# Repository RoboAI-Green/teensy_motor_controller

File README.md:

# teensy_motor_controller
Teensy Motor Controller

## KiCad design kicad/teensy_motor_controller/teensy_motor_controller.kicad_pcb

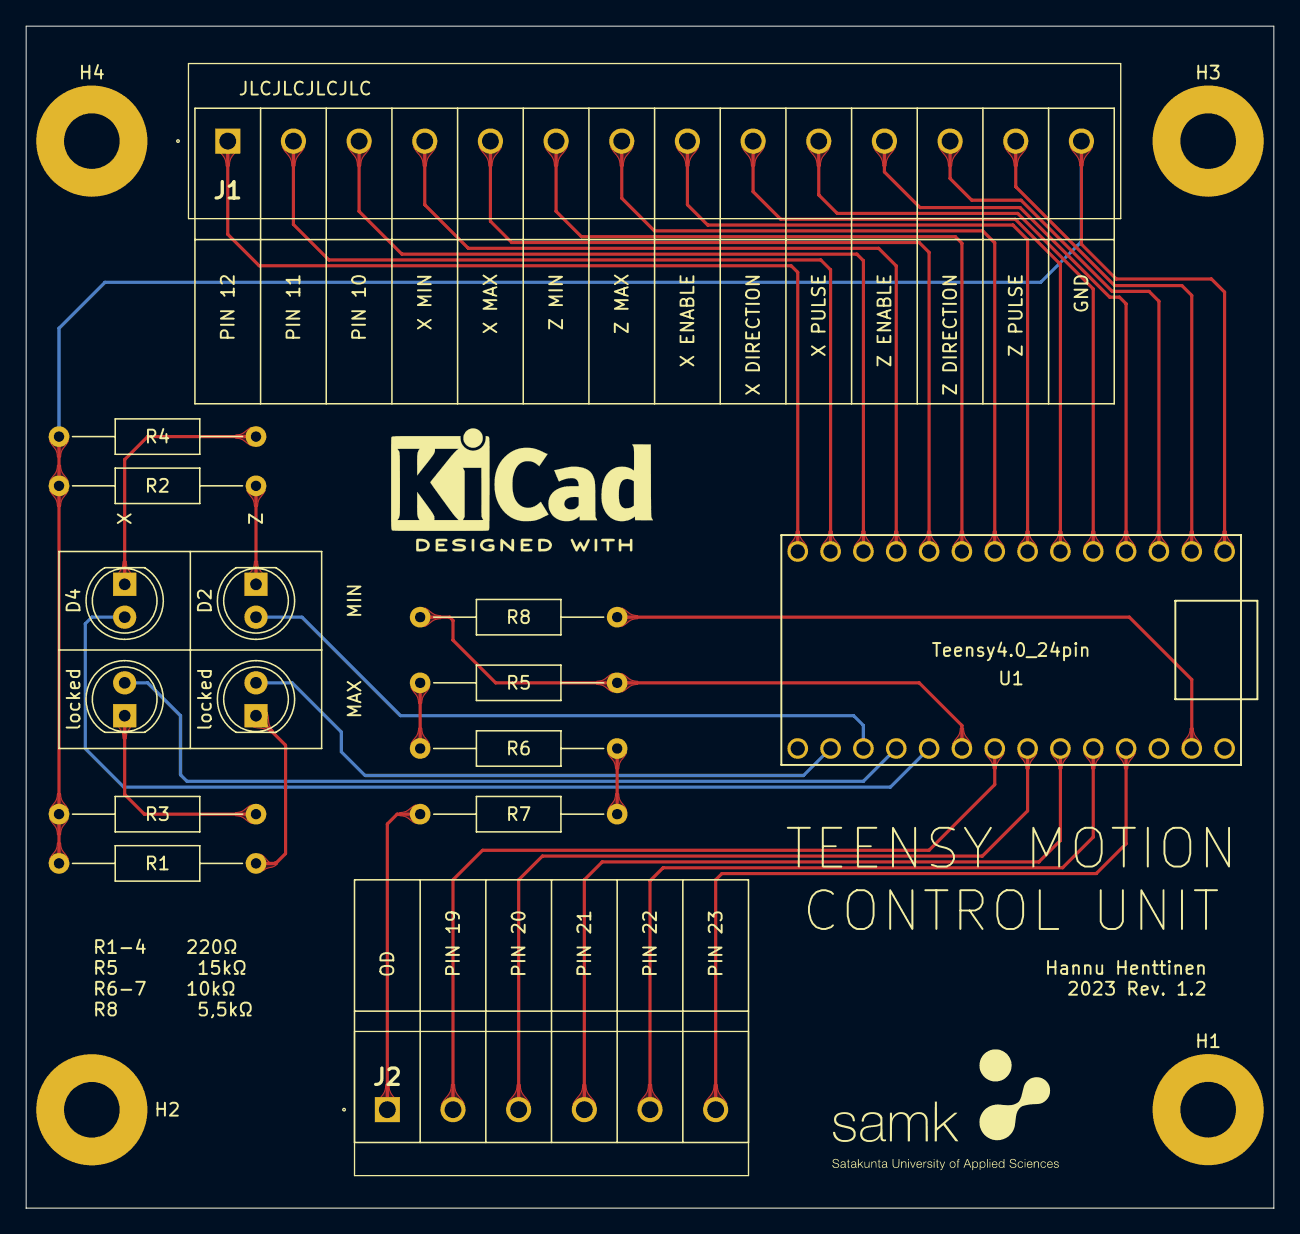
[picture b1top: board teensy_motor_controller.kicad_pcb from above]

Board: 2 copper layers, 96.5 x 91.4 mm, 19 parts (0 on the bottom side), 32 nets.

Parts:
D2, D4: LED; LED_D5.0mm
H1, H2, H3, H4: MountingHole; MountingHole_4.3mm_M4_Pad
J1: 1869334
J2: 1730162
R1, R2, R3, R4: 220; R_Axial_DIN0207_L6.3mm_D2.5mm_P15.24mm_Horizontal
R5: R15k; R_Axial_DIN0207_L6.3mm_D2.5mm_P15.24mm_Horizontal
R6, R7: R10k; R_Axial_DIN0207_L6.3mm_D2.5mm_P15.24mm_Horizontal
R8: R5,5k; R_Axial_DIN0207_L6.3mm_D2.5mm_P15.24mm_Horizontal
U1: Teensy4.0_24pin; Teensy40_24pin
locked: LED; LED_D5.0mm
locked#2: LED; LED_D5.0mm

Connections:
/X_max_led: U1.16 (16_A2_RX4_SCL1), locked.2 (A)
/X_max_limit: J1.5, U1.8 (8_TX2_IN1)
/X_min_led: D4.2 (A), U1.17 (17_A3_TX4_SDA1)
/X_min_limit: J1.4, U1.9 (9_OUT1C)
/X_stepper_direction: J1.9, U1.4 (4_BCLK2)
/X_stepper_enable: J1.8, U1.5 (5_IN2)
/X_stepper_pulse: J1.10, U1.3 (3_LRCLK2)
/Z_max_led: U1.14 (14_A0_TX3_SPDIF_OUT), locked#2.2 (A)
/Z_max_limit: J1.7, U1.6 (6_OUT1D)
/Z_min_led: D2.2 (A), U1.15 (15_A1_RX3_SPDIF_IN)
/Z_min_limit: J1.6, U1.7 (7_RX2_OUT1A)
/Z_stepper_direction: J1.12, U1.1 (1_TX1_CTX2_MISO1)
/Z_stepper_enable: J1.11, U1.2 (2_OUT2)
/Z_stepper_pulse: J1.13, U1.0 (0_RX1_CRX2_CS1)
unnamed: R1.2, locked#2.1 (K)
unnamed: D2.1 (K), R2.2
unnamed: R3.2, locked.1 (K)
unnamed: D4.1 (K), R4.2
unnamed: J1.1, U1.12 (12_MISO_MQSL)
unnamed: J1.2, U1.11 (11_MOSI_CTX1)
unnamed: J1.3, U1.10 (10_CS_MQSR)
unnamed: J1.14, R1.1, R2.1, R3.1, R4.1, U1.GND1 (GND)
unnamed: J2.1, R7.2
unnamed: J2.2, U1.19 (19_A5_SCL0)
unnamed: J2.3, U1.20 (20_A6_TX5_LRCLK1)
unnamed: J2.4, U1.21 (21_A7_RX5_BCLK1)
unnamed: J2.5, U1.22 (22_A8_CTX1)
unnamed: J2.6, U1.23 (23_A9_CRX1_MCLK1)
unnamed: R5.1, R6.1
unnamed: R5.2, R8.2, U1.18 (18_A4_SDA0)
unnamed: R6.2, R7.1
unnamed: R8.1, U1.GND2 (0_RX1_CRX2_CS1)

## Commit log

2022-04-13 Basic serial interaction set
2022-04-14 Added schematic
2022-04-22 Added script to edit VID/PID
2022-05-12 Serial communication
2022-05-20 WIP logic of limit switches and movement
2022-05-25 Added some AccelStepper commands
2022-08-09 Updated error handeling.
2022-10-26 adding submodules
2023-09-26 Added sick laser toggle function
2023-09-26 Cleaned the code little bit and added few comments
2023-10-09 New functionality
2023-10-10 Added a line to get the speed/accel info
2023-10-10 removed println and replaced it with print
2023-10-10 Forgot to add \n to one part
2023-10-11 Linear movement
2023-10-11 Updated for serial output
2023-11-06 Linear mov now returns EOL character
2024-04-19 Trying a new structure to parse commands.
2024-04-25 Parameters are now splitted into an array from space
2024-06-15 Working XY carriage
2024-06-15 Removed KiCad folder, since PCB is designed in another repository.
2024-06-17 Added parameters for pulses per mm and converted input from steps to mm for movement.
2024-06-18 Changed how lines end and streamlined commands.
2024-06-18 Changed initial_move, move_x, and move_y to use float instead of int, for sub mm movement.
2024-06-19 Added EEPROM functionality
2024-06-19 Added some comments, will need to do more.
2024-07-15 Added commands to toggle laser, get distance, and a height map function
2024-07-26 Added Z homing function and created a StepperDriver structure.
2024-07-29 Limit switches added to prevent crashes
2024-07-31 Commented the code and cleaned it a little bit
2024-08-07 Updated an error out of the initial move setting
2024-08-07 Modified the Z homing to update the distance every step
2024-08-08 Possible solution for getting Z homed faster
2024-08-08 added message that ouputs a message, if pulse count has changed
2024-08-08 Moved homez before gridMove
2024-08-08 Added timeit function, that will time how many millis it took to get a reading from distance sensor
2024-08-08 Z homing works now for the grid
2024-08-08 Added printout for the Z homing distance.
2024-08-13 Fixed a number type error. Int was used instead of float
2024-08-13 Added distance adjustment after grid initial move
2024-09-05 Added functionality for grid Z-offsetting option
2024-10-22 Added Z-correction limit while doing grid movement
